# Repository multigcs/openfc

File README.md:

OpenFC is an new Open-Hardware Flight-Controller

Standard-Size: 50x50mm (45x45mm holes) 

CPU: STM32F405 @ 168MHZ

Gyro/ACC: MPU6000 (SPI)

Compass: HMC5983 (SPI)

Baro: MS5611 (SPI)

Serial-Ports for GPS, Telemetry and SBUS

8 PWM-ESC-Connectors + CAN-Bus

PPM and SBUS inputs

microSD slot

Autoquad software compatible (Board M4r6) (https://code.google.com/p/autoquad/)

Changes v0.9:

	* initial Version
	* 2 errors in the Layout, but working

Changes v0.91: 

	* untested
	* bugfixes of v0.9
	* LED-Postion moved
	* SBUS-Inverter added

First IMU-Test: https://www.youtube.com/watch?v=cWaLLEZJb3Y

First Flight-Test: https://www.youtube.com/watch?v=trHpGgnNXYM

First Poshold-Test: https://www.youtube.com/watch?v=XDp27G_Ods4

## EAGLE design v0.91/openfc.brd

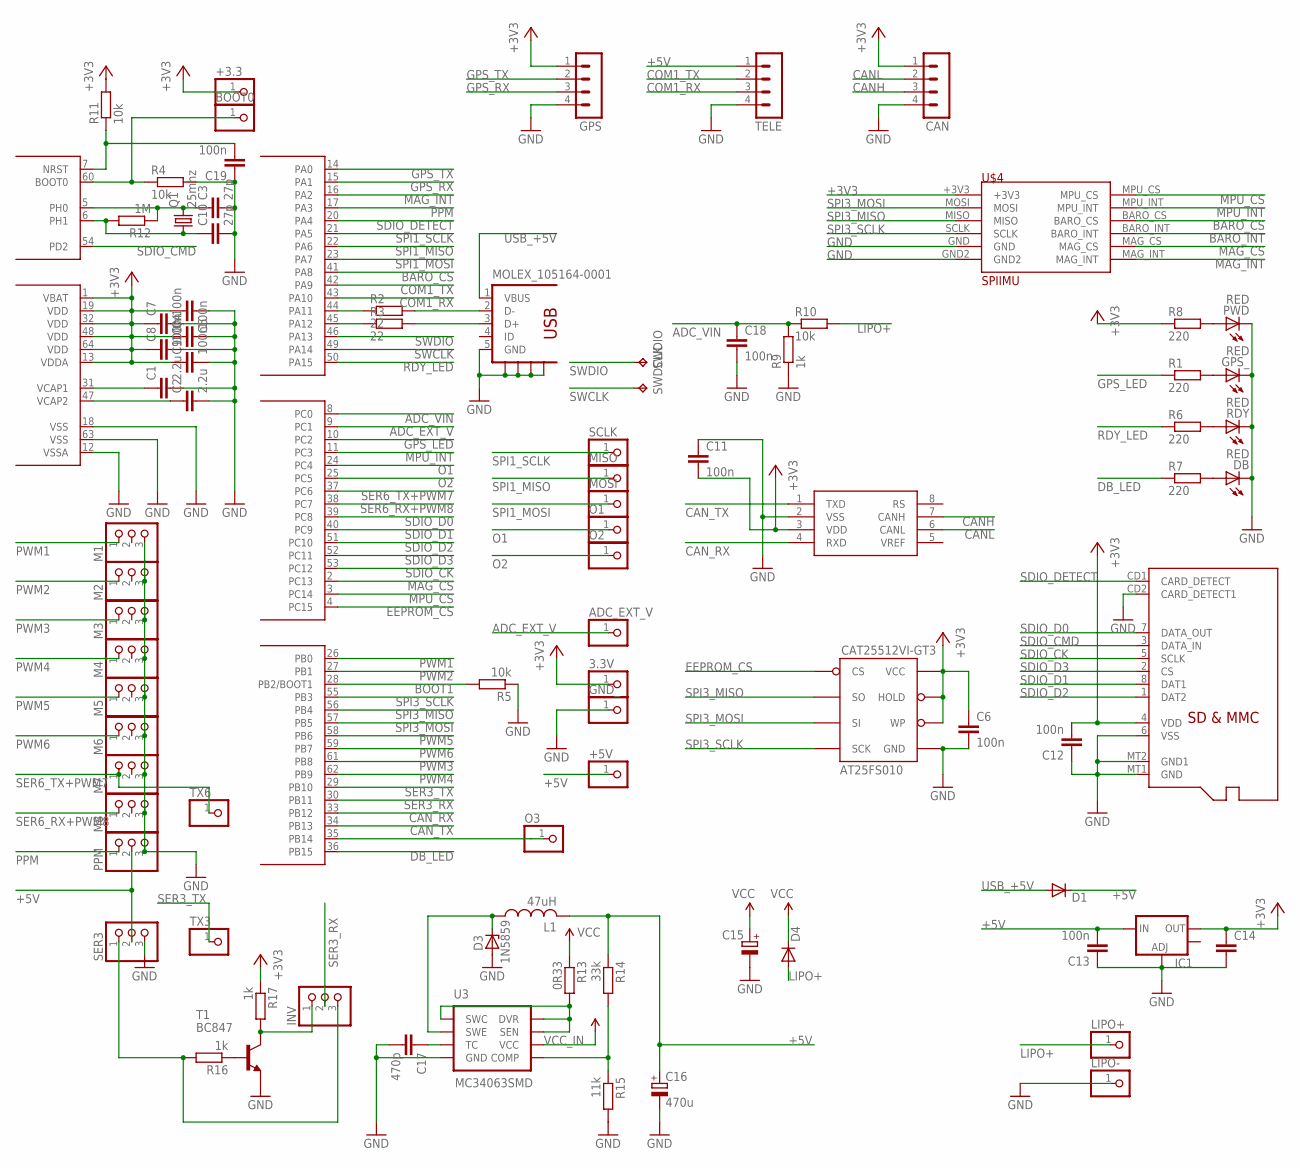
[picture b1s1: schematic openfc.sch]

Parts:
3.3V: PINHD-1X1; 1X01
+3.3, +5V: PINHD-1X1; 1X01
ADC_EXT_V: PINHD-1X1; 1X01
BOOT0: PINHD-1X1; 1X01
C1, C2: 2.2u; C0603
C3, C10: 27p; C0603
C4, C5, C6, C7, C8, C9, C11, C12, C13, C18, C19: 100n; C0603
C14: C-EUC1206; C1206
C15: CPOL-EUB/3528-21R; B/3528-21R
C16: 470u; B/3528-21R
C17: 470p; C0603
CAN: MA04-1
CAT25512VI-GT3: AT25FS010; SO08WIDE
D1, D4: DIODE-SMB; SMB
D3: 1N5859; SMB
DB: RED; LED-0603
GND_: PINHD-1X1; 1X01
GPS: MA04-1
GPS_: RED; LED-0603
IC1: V_REG_LM1117SOT223; SOT223
INV: PINHD-1X3; 1X03
L1: 47uH; L1812
LIPO+: PINHD-1X1; 1X01
LIPO-: PINHD-1X1; 1X01
M1, M2, M3, M4, M5, M6, M7, M8: PINHD-1X3; 1X03
MISO: PINHD-1X1; 1X01
MOLEX_47334-0001: MICROSD
MOLEX_105164-0001: USB-5P; USB-MINI-B
MOSI: PINHD-1X1; 1X01
O1, O2, O3: PINHD-1X1; 1X01
PPM: PINHD-1X3; 1X03
PWD: RED; LED-0603
Q1: 25mhz; CTS406
R1, R6, R7, R8: 220; R0603
R2, R3: 22; R0603
R4, R5, R10, R11: 10k; R0603
R9, R16, R17: 1k; R0603
R12: 1M; R0603
R13: 0R33; R0603
R14: 33k; R0603
R15: 11k; R0603
RDY: RED; LED-0603
SCLK: PINHD-1X1; 1X01
SER3: PINHD-1X3; 1X03
SWDCLK: TPTP14SQ; TP14SQ
SWDIO: TPTP14SQ; TP14SQ
T1: BC847; SOT23
TELE: MA04-1
TX3, TX6: PINHD-1X1; 1X01
U1: STM32F4-64; SQFP-S-10X10-64
U3: MC34063SMD; SO08
U4: MCP2551; SO08
U$4: SPIIMU

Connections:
+3V3: 3.3V.1, +3.3.1, C4.1, C5.2, C6.1, C7.1, C8.1, C9.1, C11.2, C12.2, C14.1, CAN.1, CAT25512VI-GT3.3 (WP), CAT25512VI-GT3.7 (HOLD), CAT25512VI-GT3.8 (VCC), GPS.1, IC1.2 (OUT), MOLEX_47334-0001.4 (VDD), R8.1, R11.2, R17.1, U1.1 (VBAT), U1.13 (VDDA), U1.19 (VDD), U1.32 (VDD), U1.48 (VDD), U1.64 (VDD), U4.3 (VDD), U$4.+3V3
+5V: +5V.1, C13.2, C16.+, D1.C, IC1.3 (IN), L1.2, PPM.2, R14.1, SER3.2, TELE.1
ADC_EXT_V: ADC_EXT_V.1, U1.9 (PC1)
ADC_VIN: C18.1, R9.2, R10.1, U1.8 (PC0)
BARO_CS: U1.41 (PA8), U$4.BARO_CS
BARO_INT: U$4.BARO_INT
BOOT0: BOOT0.1, R4.1, U1.60 (BOOT0)
BOOT1: R5.2, U1.28 (PB2/BOOT1)
CANH: CAN.3, U4.7 (CANH)
CANL: CAN.2, U4.6 (CANL)
CAN_RX: U1.33 (PB12), U4.4 (RXD)
CAN_TX: U1.34 (PB13), U4.1 (TXD)
COM1_RX: TELE.3, U1.43 (PA10)
COM1_TX: TELE.2, U1.42 (PA9)
DB_LED: R7.1, U1.36 (PB15)
EEPROM_CS: CAT25512VI-GT3.1 (CS), U1.4 (PC15)
GND: C1.2, C2.2, C3.2, C4.2, C5.1, C6.2, C7.2, C8.2, C9.2, C10.2, C11.1, C12.1, C13.1, C14.2, C15.-, C16.-, C17.2, C18.2, C19.1, CAN.4, CAT25512VI-GT3.4 (GND), D3.A, DB.C, GND_.1, GPS.4, GPS_.C, IC1.1 (ADJ), LIPO-.1, M1.3, M2.3, M3.3, M4.3, M5.3, M6.3, M7.3, M8.3, MOLEX_47334-0001.6 (VSS), MOLEX_47334-0001.CD2 (CARD_DETECT1), MOLEX_47334-0001.MT1 (GND), MOLEX_47334-0001.MT2 (GND1), MOLEX_105164-0001.5 (GND), MOLEX_105164-0001.S1, MOLEX_105164-0001.S2, MOLEX_105164-0001.S3, MOLEX_105164-0001.S4, PPM.3, PWD.C, R4.2, R5.1, R9.1, R15.2, RDY.C, SER3.3, T1.2 (E), TELE.4, U1.12 (VSSA), U1.18 (VSS), U1.63 (VSS), U3.4 (GND), U4.2 (VSS), U$4.GND, U$4.GND2
GPS_LED: R1.1, U1.10 (PC2)
GPS_RX: GPS.3, U1.15 (PA1)
GPS_TX: GPS.2, U1.14 (PA0)
LIPO+: D4.A, LIPO+.1, R10.2
MAG_CS: U1.2 (PC13), U$4.MAG_CS
MAG_INT: U1.16 (PA2), U$4.MAG_INT
MPU_CS: U1.3 (PC14), U$4.MPU_CS
MPU_INT: U1.11 (PC3), U$4.MPU_INT
unnamed: C2.1, U1.47 (VCAP2)
unnamed: C1.1, U1.31 (VCAP1)
unnamed: C19.2, R11.1, U1.7 (NRST)
unnamed: PWD.A, R8.2
unnamed: GPS_.A, R1.2
unnamed: R6.2, RDY.A
unnamed: DB.A, R7.2
unnamed: R16.1, T1.1 (B)
unnamed: C3.1, Q1.3 (2), R12.1, U1.5 (PH0)
unnamed: C10.1, Q1.1, R12.2, U1.6 (PH1)
unnamed: R2.1, U1.44 (PA11)
unnamed: R3.1, U1.45 (PA12)
unnamed: C17.1, U3.3 (TC)
unnamed: D3.C, L1.1, U3.2 (SWE)
unnamed: R14.2, R15.1, U3.5 (COMP)
unnamed: R13.2, U3.1 (SWC), U3.7 (SEN), U3.8 (DVR)
O1: O1.1, U1.24 (PC4)
O2: O2.1, U1.25 (PC5)
O3: O3.1, U1.35 (PB14)
PPM: PPM.1, U1.17 (PA3)
PWM1: M1.1, U1.26 (PB0)
PWM2: M2.1, U1.27 (PB1)
PWM3: M3.1, U1.61 (PB8)
PWM4: M4.1, U1.62 (PB9)
PWM5: M5.1, U1.58 (PB6)
PWM6: M6.1, U1.59 (PB7)
RDY_LED: R6.1, U1.50 (PA15)
SDIO_CK: MOLEX_47334-0001.5 (SCLK), U1.53 (PC12)
SDIO_CMD: MOLEX_47334-0001.3 (DATA_IN), U1.54 (PD2)
SDIO_D0: MOLEX_47334-0001.7 (DATA_OUT), U1.39 (PC8)
SDIO_D1: MOLEX_47334-0001.8 (DAT1), U1.40 (PC9)
SDIO_D2: MOLEX_47334-0001.1 (DAT2), U1.51 (PC10)
SDIO_D3: MOLEX_47334-0001.2 (CS), U1.52 (PC11)
SDIO_DETECT: MOLEX_47334-0001.CD1 (CARD_DETECT), U1.20 (PA4)
SER3_RX: INV.2, U1.30 (PB11)
SER3_RX_INV: INV.1, R17.2, T1.3 (C)
SER3_RX_NORM: INV.3, R16.2, SER3.1
SER3_TX: TX3.1, U1.29 (PB10)
SER6_RX+PWM8: M8.1, U1.38 (PC7)
SER6_TX+PWM7: M7.1, TX6.1, U1.37 (PC6)
SPI1_MISO: MISO.1, U1.22 (PA6)
SPI1_MOSI: MOSI.1, U1.23 (PA7)
SPI1_SCLK: SCLK.1, U1.21 (PA5)
SPI3_MISO: CAT25512VI-GT3.2 (SO), U1.56 (PB4), U$4.MISO
SPI3_MOSI: CAT25512VI-GT3.5 (SI), U1.57 (PB5), U$4.MOSI
SPI3_SCLK: CAT25512VI-GT3.6 (SCK), U1.55 (PB3), U$4.SCLK
SWCLK: SWDCLK.TP, U1.49 (PA14)
SWDIO: SWDIO.TP, U1.46 (PA13)
USB_+5V: D1.A, MOLEX_105164-0001.1 (VBUS)
USB_D+: MOLEX_105164-0001.3 (D+), R3.2
USB_D-: MOLEX_105164-0001.2 (D-), R2.2
VCC_IN: C15.+, D4.C, R13.1, U3.6 (VCC)

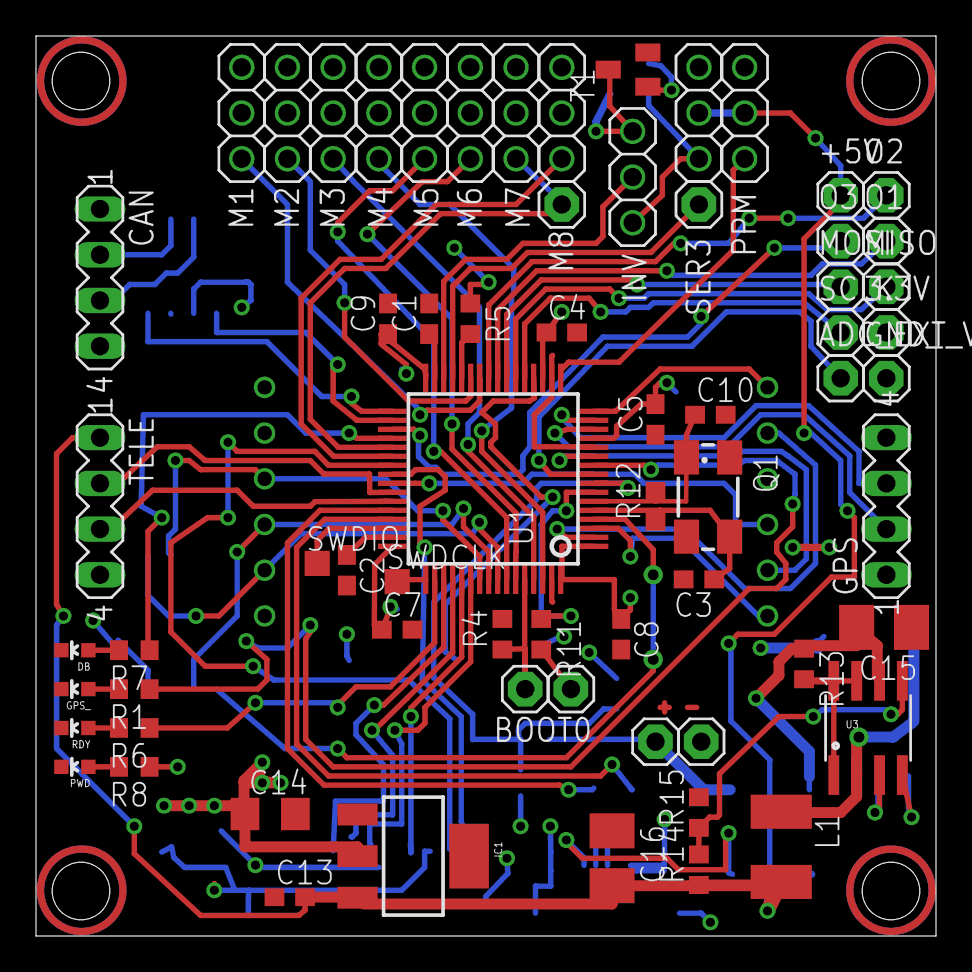
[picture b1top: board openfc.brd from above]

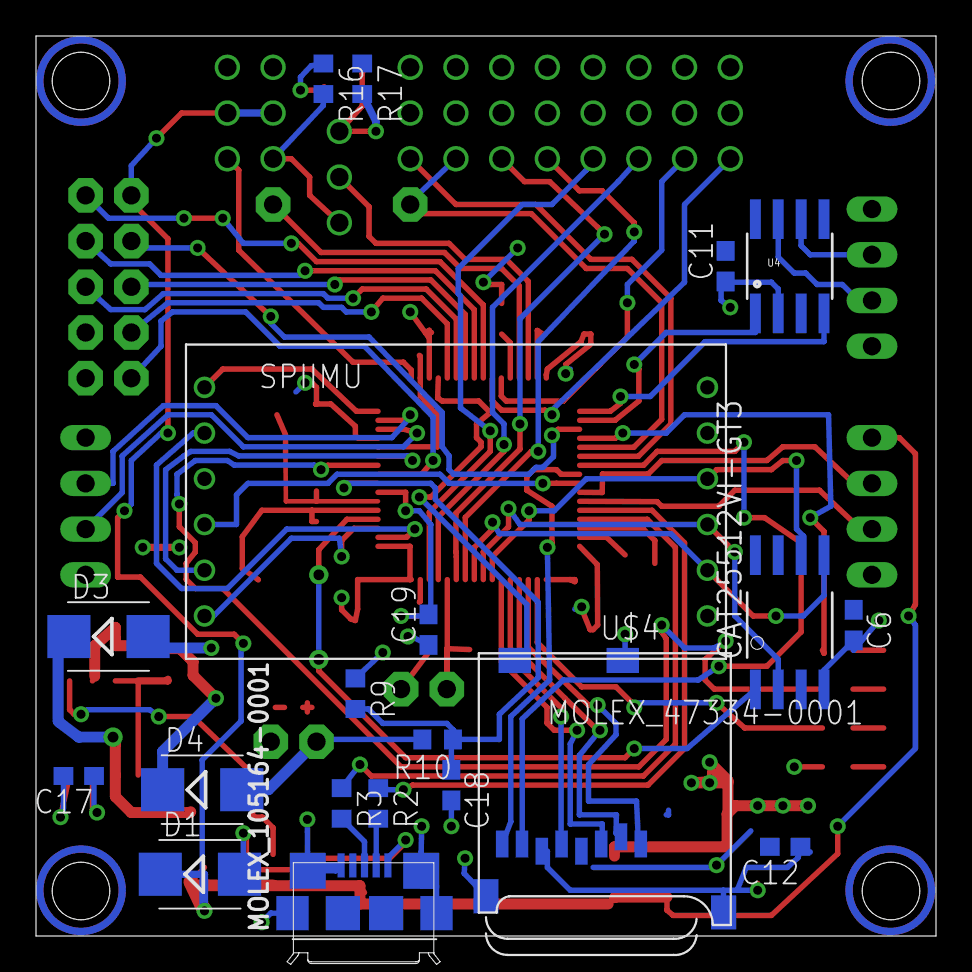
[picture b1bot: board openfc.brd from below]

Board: 2 copper layers, 50.0 x 50.0 mm, 86 parts (20 on the bottom side), 76 nets.

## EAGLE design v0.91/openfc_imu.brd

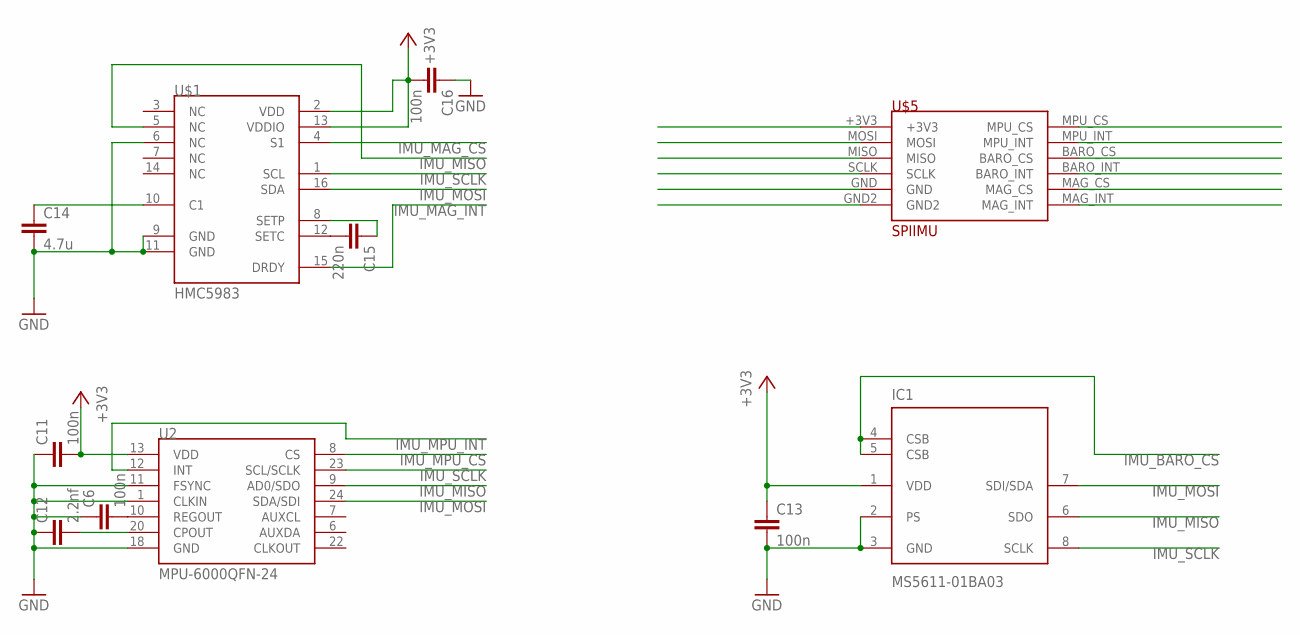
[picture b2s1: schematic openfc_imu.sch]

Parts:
C6, C11, C13, C16: 100n; C0603
C12: 2.2nf; C0603
C14: 4.7u; C0603
C15: 220n; C0603
IC1: MS5611-01BA03; SON125P300X500X100-8N
U2: MPU-6000QFN-24; QFN-24-TESTING
U$1: HMC5983; 16LPCC
U$5: SPIIMU

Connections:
IMU+3V3: C11.2, C13.1, C16.2, IC1.1 (VDD), U2.13 (VDD), U$1.2 (VDD), U$1.13 (VDDIO), U$5.+3V3
IMU_BARO_CS: IC1.4 (CSB), IC1.5 (CSB), U$5.BARO_CS
IMU_BARO_INT: U$5.BARO_INT
IMU_GND: C6.1, C11.1, C12.1, C13.2, C14.2, C16.1, IC1.2 (PS), IC1.3 (GND), U2.1 (CLKIN), U2.11 (FSYNC), U2.18 (GND), U$1.6 (NC), U$1.9 (GND), U$1.11 (GND), U$5.GND, U$5.GND2
IMU_MAG_CS: U$1.4 (S1), U$5.MAG_CS
IMU_MAG_INT: U$1.15 (DRDY), U$5.MAG_INT
IMU_MISO: IC1.6 (SDO), U2.9 (AD0/SDO), U$1.5 (NC), U$5.MISO
IMU_MOSI: IC1.7 (SDI/SDA), U2.24 (SDA/SDI), U$1.16 (SDA), U$5.MOSI
IMU_MPU_CS: U2.8 (CS), U$5.MPU_CS
IMU_MPU_INT: U2.12 (INT), U$5.MPU_INT
IMU_SCLK: IC1.8 (SCLK), U2.23 (SCL/SCLK), U$1.1 (SCL), U$5.SCLK
unnamed: C6.2, U2.10 (REGOUT)
unnamed: C14.1, U$1.10 (C1)
unnamed: C12.2, U2.20 (CPOUT)
unnamed: C15.1, U$1.8 (SETP)
unnamed: C15.2, U$1.12 (SETC)

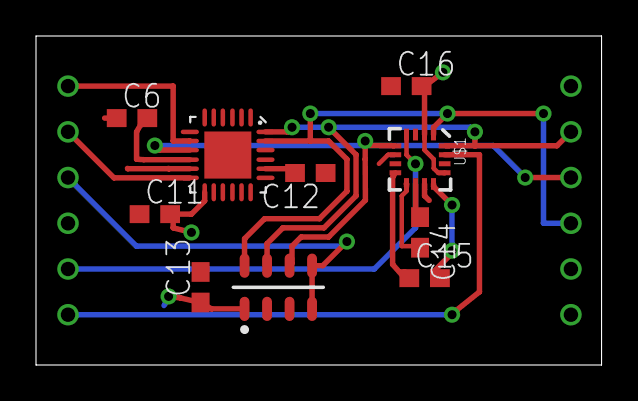
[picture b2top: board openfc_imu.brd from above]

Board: 2 copper layers, 31.4 x 18.3 mm, 11 parts (1 on the bottom side), 15 nets.

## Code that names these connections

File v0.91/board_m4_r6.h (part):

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#define SDIO_DMA_IRQn			DMA2_Stream3_IRQn
//#define SDIO_POWER_PORT			GPIOC
//#define SDIO_POWER_PIN			GPIO_Pin_5
#define SDIO_DETECT_GPIO_PORT		GPIOA
#define SDIO_DETECT_PIN			GPIO_Pin_4
#define SDIO_DETECT_PORT_SOURCE		EXTI_PortSourceGPIOA
#define SDIO_DETECT_PIN_SOURCE		EXTI_PinSource4
#define SDIO_DETECT_IRQ			EXTI4_IRQn
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    PWM_NUM_PORTS
};

#define PPM_PWM_CHANNEL		8	// which PWM channel to use for PPM capture

#define PWM_TIMERS  const TIM_TypeDef *pwmTimers[] = { \
    TIM3, \
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

#define GPS_USART		UART4
#define GPS_LED_PORT		GPIOC
#define GPS_LED_PIN		GPIO_Pin_2


#define ADC_DMA_STREAM		DMA2_Stream4
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#define CANx			    CAN2
#define CAN_CLK			    (RCC_APB1Periph_CAN1 | RCC_APB1Periph_CAN2)
#define CAN_GPIO_PORT		    GPIOB
#define CAN_RX_PIN		    GPIO_Pin_12
#define CAN_TX_PIN		    GPIO_Pin_13
#define CAN_AF_PORT		    GPIO_AF_CAN2
#define CAN_RX_SOURCE		    GPIO_PinSource12
#define CAN_TX_SOURCE		    GPIO_PinSource13
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
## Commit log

2015-03-25 add version 0.9
2015-03-25 add version 0.91
2015-03-25 v0.91: add screenshot
2015-03-25 add text and screenshot to readme
2015-03-25 add modified board-configuration files for autoquad
2015-03-25 add short changelog to readme
2015-03-25 add some video's to readme
2015-03-25 readme: fix
2015-03-25 add copyright file
2015-03-25 readme: more infos
2015-03-25 v0.9: add image
2015-03-25 v0.9: resize image
2015-03-25 readme add image
2015-03-25 readme changes

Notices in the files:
v0.91/board_m4_r6.h:
AutoQuad is free software: you can redistribute it and/or modify
it under the terms of the GNU General Public License as published by
the Free Software Foundation, either version 3 of the License, or
(at your option) any later version.
Copyright © 2011-2014  Bill Nesbitt
parts and their libraries:
SparkFun-DigitalIC: Licensing: CC v3.0 Share-Alike You are welcome to use this library for commercial purposes.
